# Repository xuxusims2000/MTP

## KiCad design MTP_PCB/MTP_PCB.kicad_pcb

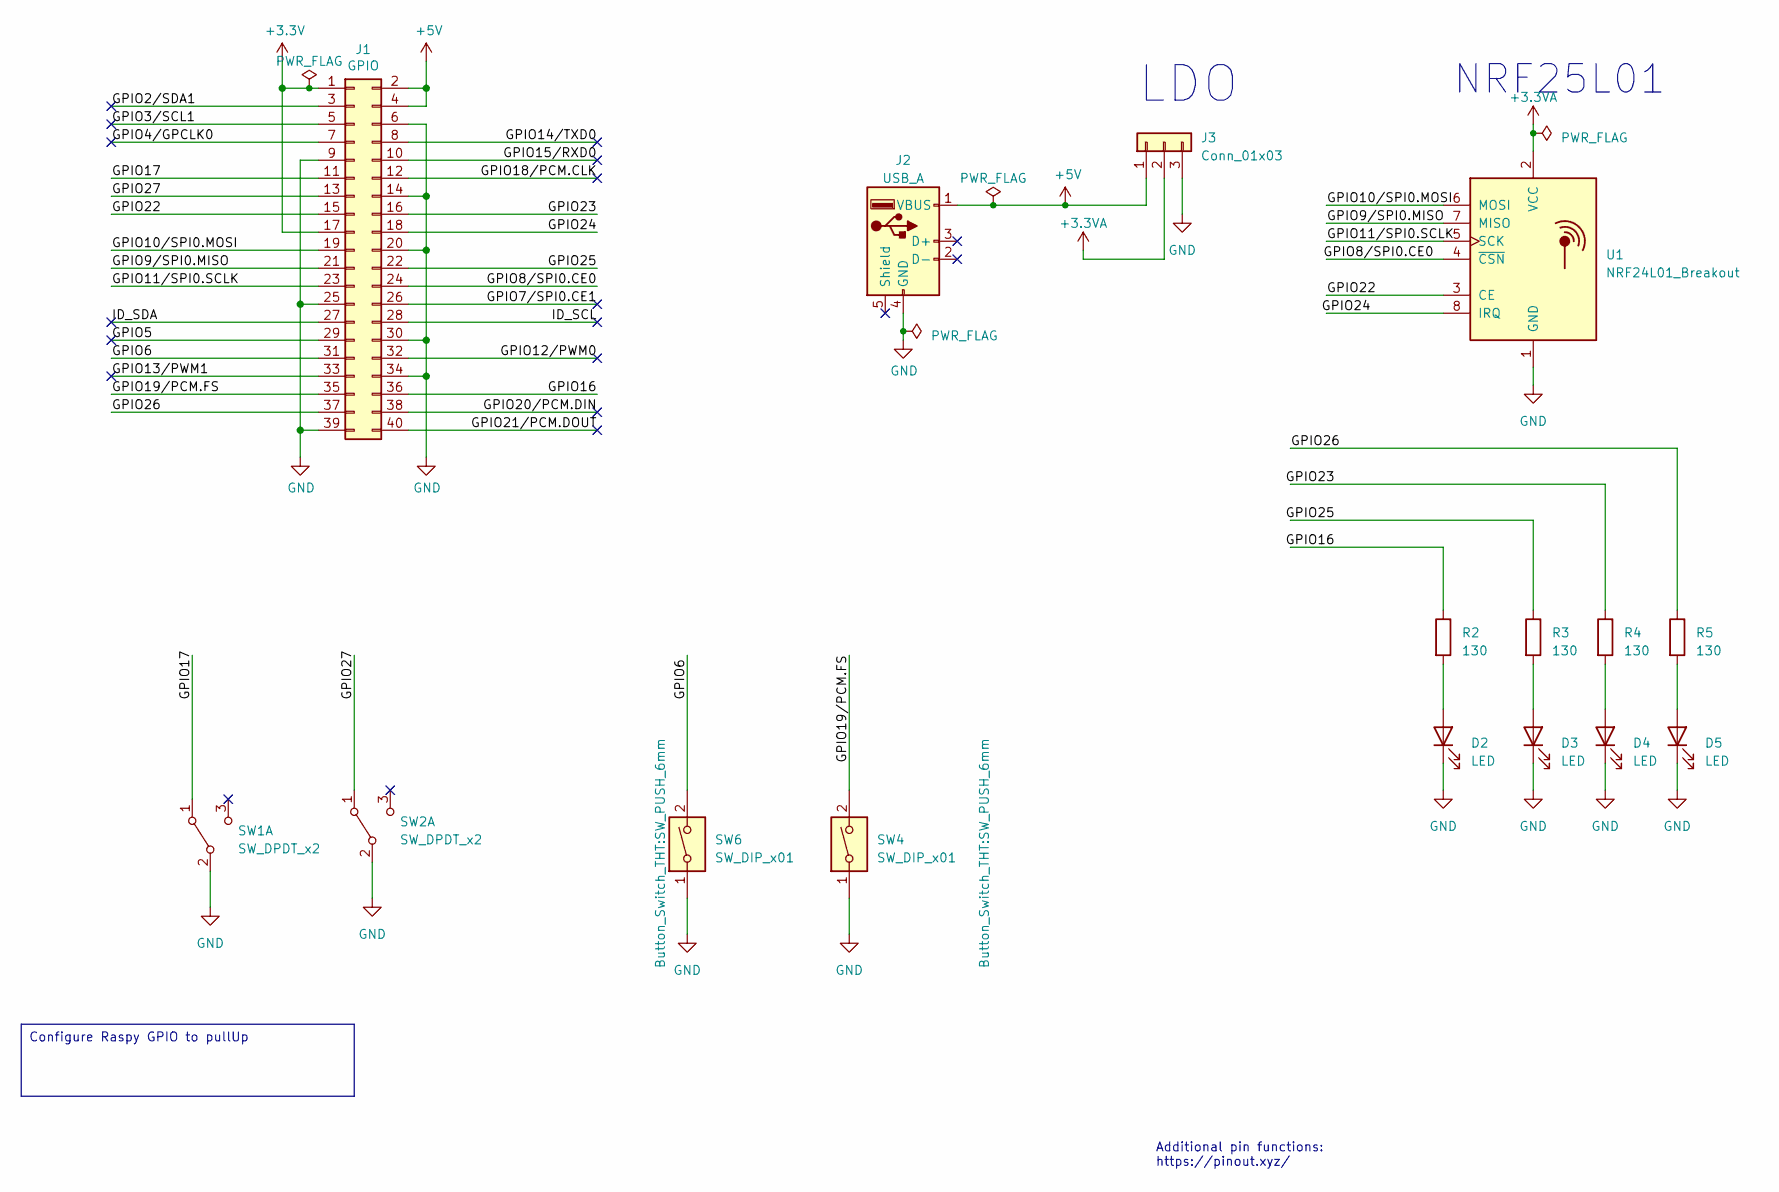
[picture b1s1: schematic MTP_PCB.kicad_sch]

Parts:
D2, D3, D4, D5: LED; LED_1206_3216Metric_Pad1.42x1.75mm_HandSolder
J1: GPIO; PinSocket_2x20_P2.54mm_Vertical
J2: USB_A; USB_A_Molex_67643_Horizontal
J3: Conn_01x03; PinSocket_1x03_P2.54mm_Vertical
R2, R3, R4, R5: 130; R_1206_3216Metric_Pad1.30x1.75mm_HandSolder
SW1, SW2: SW_DPDT_x2; SW_MTS102_3Pins_2Positions
SW4, SW6: SW_DIP_x01; SW_PUSH_6mm
U1: NRF24L01_Breakout; nRF24L01_Breakout

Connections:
+3.3VA: J3.2, U1.2 (VCC)
+3V3: J1.1, J1.17
+5V: J1.2, J1.4, J2.1 (VBUS), J3.1
/GPIO2/SDA1: J1.3
/GPIO3/SCL1: J1.5
/GPIO4/GPCLK0: J1.7
/GPIO5: J1.29
/GPIO6: J1.31, SW6.2
/GPIO7/SPI0.CE1: J1.26
/GPIO8/SPI0.CE0: J1.24, U1.4 (~CSN)
/GPIO9/SPI0.MISO: J1.21, U1.7 (MISO)
/GPIO10/SPI0.MOSI: J1.19, U1.6 (MOSI)
/GPIO11/SPI0.SCLK: J1.23, U1.5 (SCK)
/GPIO12/PWM0: J1.32
/GPIO13/PWM1: J1.33
/GPIO14/TXD0: J1.8
/GPIO15/RXD0: J1.10
/GPIO16: J1.36, R2.1
/GPIO17: J1.11, SW1.1 (A)
/GPIO18/PCM.CLK: J1.12
/GPIO19/PCM.FS: J1.35, SW4.2
/GPIO20/PCM.DIN: J1.38
/GPIO21/PCM.DOUT: J1.40
/GPIO22: J1.15, U1.3 (CE)
/GPIO23: J1.16, R4.1
/GPIO24: J1.18, U1.8 (IRQ)
/GPIO25: J1.22, R3.1
/GPIO26: J1.37, R5.1
/GPIO27: J1.13, SW2.1 (A)
/ID_SCL: J1.28
/ID_SDA: J1.27
GND: D2.1 (K), D3.1 (K), D4.1 (K), D5.1 (K), J1.6, J1.9, J1.14, J1.20, J1.25, J1.30, J1.34, J1.39, J2.4 (GND), J3.3, SW1.2 (B), SW2.2 (B), SW4.1, SW6.1, U1.1 (GND)
unnamed: D2.2 (A), R2.2
unnamed: D3.2 (A), R3.2
unnamed: D4.2 (A), R4.2
unnamed: D5.2 (A), R5.2

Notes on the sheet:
Configure Raspy GPIO to pullUp
LDO
Additional pin functions: https://pinout.xyz/
NRF25L01

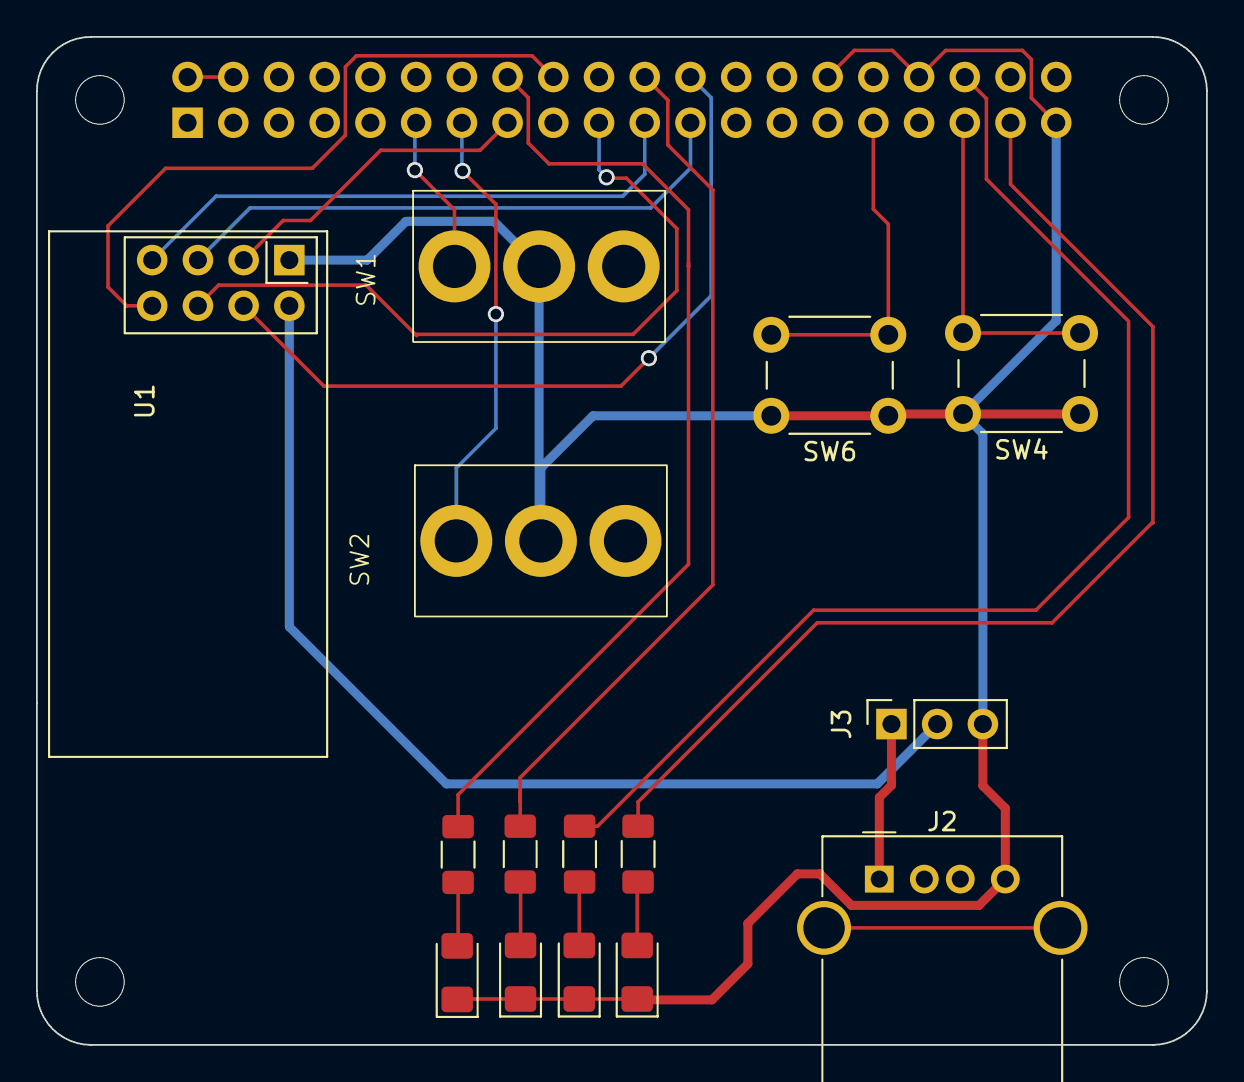
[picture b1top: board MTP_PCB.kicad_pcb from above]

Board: 2 copper layers, 65.0 x 56.0 mm, 20 parts (1 on the bottom side), 22 nets.

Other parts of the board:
MH1, MH2, MH3, MH4: MountingHole_2.7mm_M2.5

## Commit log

2025-11-06 first version PCB finished
2025-11-10 remove GND planes
